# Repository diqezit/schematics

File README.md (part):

<details>
<summary><b>Русская версия README</b></summary>

# FMradio

ЧМ-приёмник на дискретных транзисторах с низкой промежуточной частотой, зарядовым частотным детектором, варикапной настройкой, автоматической подстройкой частоты и УНЧ на LM386.

- Диапазон: 88-108 МГц
- Питание: +9 В
- Нагрузка: 8 Ом
- Целевой размер платы: 50 x 70 мм
- Ток покоя тракта до УНЧ: около 23 мА

> Статус: инженерный разбор схемы и наброска печатной платы. Источник истины по номиналам и режимам - LTspice, файл `Fm.asc` (ревизия 05). Файл Multisim `Fm.ms14` сохранён как историческая ссылка предварительной серии ревизии 01 и для сверки топологии KiCad. Это не подтверждение работоспособности готового устройства и не комплект для изготовления.

Изменения ревизии 05:

1. Варикапы D1 входного контура и D5 гетеродина заменены с BB112 на BB844. Принята модель Cjo = 120 пФ, Vj = 0,75 В, M = 1,35. Расчётная кривая C(V) сверена с опорной таблицей, отклонение меньше 1 %.
2. Транзистор гетеродина 2N5401 заменён на BFT92. Для 2N5401 с fT = 300 МГц запуска на 101,9 МГц не получено из-за недостаточного запаса по граничной частоте. Для BFT92 паспортное fT равно 5 ГГц, упрощённая SPICE-модель даёт около 1 ГГц.
3. Пересчитаны контуры: L1 = 175 нГн, C3 = 4,1 пФ, C4 = 13,7 пФ; L2 = 138 нГн, C17 = 10 пФ, C18 = 36 пФ, C19 = 13,7 пФ.
4. Добавлена директива `.ic` для короткого окна звукового тракта без ожидания установления медленной петли АПЧ.
5. Нагрузка R22/C22 в АПЧ увеличена до R22 = 15 кОм и C22 = 47 мкФ. Расчётная постоянная времени составляет около 0,7 с.

Правило трёх документов. Номиналы и режимы нормативны по LTspice. Топология и посадочные места нормативны по KiCad. Расчётные формулы разделов 1-7 записаны в нумерации KiCad/README и сверяются с LTspice по таблице соответствия. Перенумерация KiCad под ревизию 05 запланирована; до её выполнения таблица соответствия нормативна.

Расчётные величины в основных разделах получены аналитически для режимов по постоянному току и RC-цепей при U_БЭ около 0,65 В и типичном h21э транзисторов. Результаты симуляции сведены в приложении, совпадения и расхождения с расчётом отмечены явно. Ни расчёт, ни симуляция не заменяют измерений на реальной плате.

## Схема

## Демонстрация работы

Снимок относится к одному из прогонов подгонки контуров ревизии 01 в Multisim и служит только иллюстрацией настройки. Рабочие данные ревизии 05 сняты в LTspice командой `.tran 0 12m 10m 1n`. Raw-файл или экспорт ключевых трасс следует хранить вместе с `Fm.asc`.

## Источники и воспроизводимость

- `Fm_radio.kicad_sch`: схема, KiCad 10.0, лист A3.
- `Fm_radio.kicad_pcb`: печатная плата, KiCad 10.0, два слоя меди F.Cu и B.Cu.
- `Fm_radio.kicad_pro`: настройки проекта, включая правила проверки платы.
- `Fm_radio.kicad_prl`: локальные настройки отображения.
- `Fm.asc`: файл симуляции LTspice, источник истины начиная с ревизии 02. Содержит нетлист, директивы `.tran`, `.op`, `.ic`, `.options`, модели диодов, варикапов и транзистора гетеродина.
- `Fm.ms14`: файл симуляции Multisim. Содержит экспорт предварительной серии ревизии 01 и замеры рабочей точки. Результаты ревизий 02-05 из него не воспроизводятся и не цитируются как текущие.

## Инструмент моделирования и соответствие ревизий

Начиная с ревизии 02 источником истины по номиналам и режимам является LTspice. Multisim оставлен как историческая ссылка ревизии 01 и средство сверки топологии KiCad.

LTspice выбран из-за доступных допусков интегрирования, именованных измерений, `.step`, `.meas`, `.op` и приемлемого времени расчёта. В Multisim непрерывные окна 300 мкс и 3 мс были практически недоступны, а встроенный частотомер давал ложные показания на узлах с амплитудой в десятки милливольт.

Модели LTspice, источник истины ревизии 05:

```text
.model BB844 D(Is=1e-14 Rs=0.28 N=1.0 Cjo=120p M=1.35 Vj=0.75 Fc=0.5
+ Bv=18 Ibv=10u Tt=0 Eg=1.11 Xti=3)

.model BFT92 PNP(IS=1E-14 BF=100 VAF=100 IKF=0.1 ISE=1E-13 NE=1.5
+ BR=4 IKR=0.1 ISC=1E-13 NC=1.5 RB=10 RE=1 RC=10
+ CJE=1.5P VJE=0.7 MJE=0.4 CJC=1P VJC=0.5 MJC=0.4
+ TF=0.15N TR=10N XTB=1.5 XTI=3 EG=1.11)

.model BZX55C6V8 D(Is=1e-14 N=1.1 Rs=3.5 Cjo=160p M=0.33 Vj=0.75 Bv=6.8 Ibv=5m Eg=1.11 Xti=3)
.model BZX55C3V3 D(Is=1e-14 N=1.1 Rs=15 Cjo=25p M=0.33 Vj=0.6 Bv=3.3 Ibv=5m)
```

Модель BB112 сохранена только для воспроизведения ревизии 04:

```text
.model BB112 D(Is=1e-14 Rs=0.7 N=1.2 Cjo=58p M=0.50 Vj=0.85 Fc=0.5 Bv=30 Ibv=10u Tt=0)
```

Упрощённая модель BFT92 с TF = 0,15 нс соответствует оценочному fT около 1 ГГц, а не паспортным 5 ГГц. Она подтверждает запуск в ревизии 05, но не заменяет модель производителя для оценки амплитуды, фазового шума и предельного режима. Имена библиотек остальных транзисторов и полные строки их SPICE-моделей в репозитории не зафиксированы, поэтому перед повторным прогоном модели следует сверить.

## Протокол прогонов

Нормативный короткий прогон ревизии 05:

```text
.tran 0 12m 10m 1n
.ic V(DETEC)=1.2 V(AFC)=1.2 V(FILT)=1.2 V(N010)=4.5 V(VZ_3V3)=3.3 V(VZ_6V8)=6.8
.options reltol=0.003 trtol=7 method=gear cshunt=1e-14 plotwinsize=0
```

Директива `.ic` задаёт начальные уровни детектора, АПЧ, фильтра, выхода LM386 и двух опорных шин. Она нужна для наблюдения последних 2 мс из окна 12 мс без ожидания установления петли АПЧ с постоянной времени около 0,7 с. Этот режим не доказывает захват АПЧ и не заменяет прогон без начальных условий.

Дополнительные прогоны:

- Рабочая точка: `.op` при V1 = 8/9/10 В, положении потенциометра 0/50/100 % и T = -10/25/50 C.
- ВЧ и ПЧ без принудительных начальных условий: не менее 300 мкс с максимальным шагом 1 нс.
- Звуковой тракт: не менее 20 мс либо до установления C25 = 330 мкФ и узла N010.
- АПЧ: 0,5-1 с без `.ic` или отдельная огибающая модель. Полный ВЧ-прогон с шагом 1 нс на таком интервале вычислительно тяжёл.
- Ограничитель: 3 мс с контролем VBE(VT5) не ниже -5 В и огибающей 1 кГц 280-400 мВ размаха.

## Нормативные пороги приёмки

Пороги ревизии 04 сохранены для исторического сравнения:

- меандр на коллекторе VT4 непрерывен до 300 мкс, без пачек и провалов;
- ток обратной связи УПЧ без дрейфа среднего;
- полка детектора 1,1-1,3 В;
- I(D6) 5-12 мА;
- V(REF) 6,4-7,2 В.

Нормативные пороги ревизии 05:

- размах на коллекторе Q6 1-2 В;
- ток эмиттера Q6 2-3 мА без двуполярных игл и выбросов;
- период импульсов ПЧ при MDI = 0 равен 2,35 +/- 0,05 мкс;
- полка детектора 1,1-1,3 В;
- I(D6) 5-12 мА;
- V(REF) 6,4-7,2 В;
- звуковой сигнал на нагрузке 8 Ом не меньше 1 В размаха после установления тракта.

Текущий прогон ревизии 05 проходит критерии периода ПЧ и полки детектора. Критерии амплитуды и тока гетеродина не пройдены. Ток D6 и установившиеся уровни опорных шин без `.ic` в предоставленных измерениях отсутствуют. Критерий звука не оценён, потому что V(N010) и C25 не установились в окне 12 мс.

## Блокеры до трассировки

- Перевозбуждение гетеродина. V(Q6_C) имеет размах 0-4 В, Ie(Q6) достигает примерно +/-6 мА. Требуется повторный расчёт смещения и коэффициента обратной связи BFT92. Плату до выбора проверенного режима не фиксировать.
- Сопряжение контуров. При одном управляющем напряжении разность резонансных частот L1 и L2 меняется примерно от 0,5 до 1,5 МГц вместо требуемых 425 кГц. Нужна раздельная коррекция ветвей D1 и D5 или подстроечные элементы.
- Ход настройки. Связка BB844 и 13,7 пФ в текущей модели даёт около 0,8 МГц, поэтому диапазон 88-108 МГц не перекрывается. Нужна коммутация L2, другой диапазон ёмкостей или отдельная грубая настройка.
- Сохраняется блокер ревизии 04: прогон 3 мс с VBE(VT5) не ниже -5 В ещё не выполнен.

Имена узлов вида n0XX не нормативны. Перед прогоном следует назначить метки A, B, REF, TUNE, Q1_E, Q2_B, Q3_B, Q4_C, Q5_C, Q6_C, DETEC, AFC, FILT, N010, SPK, VZ_3V3 и VZ_6V8.

## Таблица соответствия идентификаторов

Таблица нормативна до перенумерации KiCad.

| Назначение | KiCad/README | LTspice rev 05 | Номинал или тип |
|---|---|---|---|
| ВЧ-транзистор | VT1 2N5401 | Q1 2N5401 | режим без изменения |
| Смеситель | VT2 BF517 | Q2 2SC3838K | тип 2SC3838K |
| УПЧ 1 / УПЧ 2 | VT3 / VT4 BC547 | Q3 / Q4 BC547C | группа C |
| Ограничитель | VT5 BC547 | Q5 BC547C | группа C |
| Гетеродин | VT6 BFT92 | Q6 BFT92 | PNP, SOT-23 |
| Диоды детектора | VD1, VD2 1N4148 | D2, D3 1N4148 | без изменения |
| Опора настройки | VD3, R19 | D6 BZX55C6V8, R25 180 Ом | V(REF) около 6,86 В |
| Шина 3,3 В | VD4, R27 1 кОм | D4, R19 1 кОм | VZ_3V3 |
| Варикап входа | BB844, C4 13,7 пФ | D1 BB844, C4 13,7 пФ | Cjo = 120 пФ |
| Варикап гетеродина | BB844, C19 13,7 пФ | D5 BB844, C19 13,7 пФ | Cjo = 120 пФ |
| Входной контур | L1, C3, C4, D1 | L1 175 нГн, C3 4,1 пФ, C4 13,7 пФ | пересчитан в rev 05 |
| Контур гетеродина | L2, C17, C18, C19, D5 | L2 138 нГн, C17 10 пФ, C18 36 пФ, C19 13,7 пФ | пересчитан в rev 05 |
| Вход рейки | R2 22 Ом | R15 22 Ом | без изменения |
| Рейка A к рейке B | свободное обозначение | 100 Ом | номер сверить |
| Эмиттер ВЧ | R3 470 Ом | R1 470 Ом | без изменения |
| Делитель базы ВЧ | R4 6,8 кОм / R13 33 кОм | R2 6,8 кОм / R3 33 кОм | без изменения |
| База смесителя | R6 620 кОм | R4 620 кОм | без изменения |
| Нагрузка смесителя | R5 3 кОм, C3 47 пФ | R5 3 кОм, C6 47 пФ | 47 пФ обязателен |
| ФНЧ после смесителя | свободные обозначения | 470 Ом, 33 пФ NP0 | номера сверить с рейками |
| Серия после связи | R11 | R6 100 кОм | аттенюатор |
| ООС эмиттер-база | R12 | R7 2,2 кОм | слив заряда |
| Нагрузка УПЧ1 / УПЧ2 | R7 10 кОм / R8 2,2 кОм | R8 10 кОм / R9 2,2 кОм | без изменения |
| Эмиттер УПЧ2 | R14 470 Ом, C16 47 нФ | R10 470 Ом, C10 47 нФ | без изменения |
| База / нагрузка ограничителя | R9 47 кОм / R10 3 кОм | R12 47 кОм / R13 3 кОм | без изменения |
| Фильтр детектора | R15 10 кОм, C17 10 нФ | R12 10 кОм, C14 10 нФ | обозначения rev 05 |
| Связь смеситель-УПЧ | C8 | C7 1 нФ | без изменения |
| Связь УПЧ-ограничитель | C9 | C12 10 нФ | без изменения |
| Насос детектора | C10 | C13 39 пФ | без изменения |
| Потенциометр настройки | R21 10 кОм | U1 10 кОм | движок выставляется по периоду |
| АПЧ | R26/R25, C26 | R22 15 кОм, C22 47 мкФ | постоянная времени около 0,7 с |
| Выходной конденсатор УНЧ | C12 | C25 330 мкФ | время установления больше окна 12 мс |
| Байпас LM386 | по схеме | C27 | начальный заряд не установился |

Разделы 1-5 описывают тракт LTspice ревизии 05. Раздел 6 относится к модели и изделию с LM386. Раздел 7 совмещает топологию шин LTspice и требования к физической плате.

## Архитектура

```text
AE1 -> C6 -> Q1 / L1 / D1 -> Q2 -> Q3 -> Q4 -> Q5
                                                    |
                  LM386 <- volume <- detector <- D2 / D3 / C13
                    |                         |
                 C25 / 8R              R22 / C22 AFC
                                              |
                                 D1 / D5 / Q6 / L2
```

Сигнал антенны усиливается каскадом с общей базой и смешивается с сигналом гетеродина через магнитную связь L1-L2. Затем он проходит широкополосный бесконтурный усилитель промежуточной частоты, ограничивается и демодулируется зарядовым частотным детектором. Медленная составляющая напряжения детектора управляет варикапами через автоматическую подстройку частоты. Входной контур сопряжён с настройкой вторым варикапом BB844. Низкочастотный усилитель построен на LM386.

Элементная база ревизии 05: Q1 типа 2N5401, Q2 типа 2SC3838K, Q3-Q5 типа BC547C, Q6 типа BFT92, D1 и D5 типа BB844.

Промежуточная частота остаётся низкой:

```math
f_{IF} \approx 425 \text{ кГц}, \qquad f_{LO} = f_{RF} + 425 \text{ кГц}
```

При f_RF = 101,5 МГц целевая частота гетеродина равна примерно 101,925 МГц. Период 2,35 мкс соответствует 425 кГц. Источник SFFM с MDI = 75 и FS = 1 кГц даёт девиацию +/-75 кГц.

Низкая ПЧ не обеспечивает зеркальную избирательность. При верхней настройке зеркальный канал отстоит на 2f_IF, то есть примерно на 850 кГц, и остаётся внутри полосы входного контура. Для радикального улучшения нужен двухконтурный преселектор или двойное преобразование частоты.

## Шины питания

```text
+9 В -> развязка -> узел A -> развязка -> узел B
```

Узел A питает ограничитель. Узел B питает ВЧ-каскад, смеситель и усилитель промежуточной частоты. LM386 питается от +9 В с отдельной местной развязкой. Гетеродин BFT92 питается от шины VZ_3V3. Опора настройки D6 питается от +9 В через 180 Ом.

| Шина | Назначение | Нормальный уровень |
|---|---|---|
| +9 В | LM386, опорные стабилизаторы | 9,0 В |
| Узел A | ограничитель | после входной развязки |
| Узел B | Q1-Q4 | около 8,25-8,3 В |
| VZ_3V3 | Q6 BFT92 | 3,3 В |
| VZ_6V8 / REF | настройка и АПЧ | около 6,86 В |

Ток покоя около 23 мА относится к тракту до LM386. Ток и мощность полного изделия зависят от громкости и нагрузки 8 Ом.

## 1. Входной ВЧ-усилитель

Q1 2N5401 включён по схеме с общей базой. Сигнал антенны поступает на эмиттер через 1 нФ. Делитель 6,8 кОм / 33 кОм задаёт смещение базы, 10 нФ шунтирует базу по ВЧ, 470 Ом задаёт ток эмиттера. Коллектор нагружен контуром L1 = 175 нГн.

В ревизии 05 контур содержит C3 = 4,1 пФ и ветвь C4 = 13,7 пФ с D1 BB844. Обратное смещение D1 приходит с цепи настройки через резистор. Номиналы относятся к LTspice и не заменяют измерение реальной индуктивности, паразитной ёмкости и добротности.

Ёмкость модели BB844 оценивается выражением:

```math
C(V) = \frac{C_{jo}}{(1 + V/V_j)^M}, \qquad C_{jo}=120 \text{ пФ}, \quad V_j=0{,}75 \text{ В}, \quad M=1{,}35
```

Расчётная кривая сверена с опорной таблицей с отклонением меньше 1 %. Это подтверждает параметры модели, но не гарантирует сопряжение двух реальных контуров с разбросом L и паразитных ёмкостей.

Режим по постоянному току не менялся принципиально. В ревизии 05 Ie(Q1) около -1,47 мА. На эмиттере Q1 присутствует ВЧ-сигнал 101,5 МГц с размахом примерно 0-400 мВ, то есть сигнал доходит до входа смесителя.

Катушка L1 в исходной механике наматывается проводом 0,5 мм на оправке 5,5 мм. Число витков и шаг следует подобрать по измеренным 175 нГн, а не переносить автоматически из расчёта ревизии 04.

## 2. Смеситель

Q2 2SC3838K включён по схеме с общим эмиттером. Резистор 620 кОм задаёт ток базы, 3 кОм служит коллекторной нагрузкой, 47 пФ подавляет остатки ВЧ и ограничивает верхнюю частоту низкой ПЧ. Связь с усилителем промежуточной частоты идёт через разделительную цепь и аттенюатор 100 кОм.

Связь входного контура с базой смесителя должна иметь ёмкость порядка единиц пикофарад. Номинал 1 нФ из ранней схемы перегружает контур. Электролит 2,2 мкФ в ВЧ-узле исключается.

Полюс нагрузки смесителя:

```math
f_p = \frac{1}{2\pi \times 3\text{ кОм} \times 47\text{ пФ}} \approx 1{,}13 \text{ МГц}
```

Конденсатор 47 пФ обязателен. Без него остаток гетеродина выпрямляется следующим каскадом, Q3 насыщается, а тракт ПЧ защёлкивается.

В ревизии 05 V(Q2_B) меняется примерно от 350 до 900 мВ. Ic(Q2) меняется примерно от 0,3 до 3,6 мА. Смеситель работает в ключевом режиме, но инжекция гетеродина выше желаемой. Уменьшать её следует после нормализации режима Q6, а не случайным ослаблением ПЧ-тракта.

Магнитная связь L1-L2 остаётся двусторонней. Для платы требуются контролируемые ориентация и расстояние между катушками. Точное соответствие коэффициента K геометрии платы модель SPICE не рассчитывает.

### RC после смесителя

Дополнительный ФНЧ 470 Ом / 33 пФ должен стоять сразу после коллекторной нагрузки смесителя. Его расчётный полюс:

```math
f_p = \frac{1}{2\pi \times 470 \times 33\text{ пФ}} \approx 10{,}26 \text{ МГц}
```

На 425 кГц звено практически прозрачно, а остатки диапазона 88-108 МГц ослабляются. Обозначения этого фильтра конфликтовали с обозначениями развязки питания в ранних версиях и должны быть назначены заново в KiCad.

## 3. Усилитель промежуточной частоты

Q3 и Q4 BC547C образуют двухкаскадный усилитель с непосредственной связью. После связи со смесителем стоит 100 кОм, а с эмиттера Q4 на базу Q3 включён резистор 2,2 кОм. Эта пара ограничивает привод и отводит выпрямленный заряд за период ПЧ.

Эмиттер Q4 нагружен 470 Ом с шунтом 47 нФ. Связь с ограничителем идёт через 10 нФ. Номиналы усилителя промежуточной частоты в ревизии 05 не менялись.

Для периода 2,35 мкс постоянная времени слива около 2,2 мкс остаётся сопоставимой с одним циклом:

```math
\tau_{drain} \approx 2{,}2 \text{ кОм} \times 1 \text{ нФ} \approx 2{,}2 \text{ мкс}
```

Критерий работы каскада: непрерывные импульсы ПЧ без перехода в линейный режим и без дрейфа среднего тока обратной связи. Прямого отдельного набора измерений Q3/Q4 для ревизии 05 не предоставлено, поэтому прежние амплитуды ревизии 04 не объявляются текущими.

## 4. Ограничитель и детектор

Q5 BC547C работает ограничителем. Резистор 47 кОм задаёт ток базы, 3 кОм служит нагрузкой, эмиттер соединён с общим проводом. В ревизии 05 V(Q5_C) имеет прямоугольную форму 0-11 В с периодом 2,35 мкс, что соответствует ПЧ около 425 кГц.

Обратное напряжение база-эмиттер ограничителя остаётся открытым риском. Стандартная BJT-модель может не отражать реальный пробой. До прогона 3 мс с VBE(VT5) не ниже -5 В этот пункт не закрыт.

Зарядовый детектор построен на C13 = 39 пФ и двух 1N4148. Средний ток насоса оценивается так:

```math
I_{avg} = C \times \Delta U \times f_{IF}, \qquad U_{det} = I_{avg} \times R_{load}
```

При ПЧ около 425 кГц ожидаемая полка находится около 1,2 В. В ревизии 05 V(DETEC) равно 1,2 В, то есть детектор находится в штатной точке.

Фильтр ревизии 05 обозначен R12 = 10 кОм и C14 = 10 нФ. Без нагрузки:

```math
\tau_0 = 10 \text{ кОм} \times 10 \text{ нФ} = 100 \text{ мкс}
```

С нагрузкой цепи АПЧ эффективная постоянная времени оценивается примерно в 60 мкс. Вариант C14 = 4,7 нФ даёт 47 мкс без нагрузки, но не принят до проверки звуковой АЧХ и уровня пульсаций.

## 5. Гетеродин и автоматическая подстройка частоты

Q6 BFT92 с L2 = 138 нГн образует генератор Колпитца. Ёмкостная обратная связь задаётся C17 = 10 пФ и C18 = 36 пФ. Варикап D5 BB844 включён через C19 = 13,7 пФ. База заземлена по переменному току, питание приходит от стабилизированной шины 3,3 В.

Эквивалентная последовательная ёмкость делителя обратной связи:

```math
C_s = \frac{10 \times 36}{10 + 36} \approx 7{,}83 \text{ пФ}
```

2N5401 с модельным fT = 300 МГц не запускался на 101,9 МГц. BFT92 имеет паспортное fT = 5 ГГц, а применённая упрощённая модель соответствует примерно 1 ГГц. Замена восстановила запуск, но одновременно дала избыточную амплитуду.

Текущий результат:

- V(Q6_C) колеблется от 0 до 4 В;
- Ie(Q6) имеет выбросы примерно до +/-6 мА;
- период импульсов ПЧ равен 2,35 мкс;
- V(Q2_B) показывает избыточную инжекцию в смеситель.

Требуемый режим Q6 составляет 1-2 В размаха на коллекторе и 2-3 мА эмиттерного тока без выбросов. Номиналы коррекции обратной связи и смещения пока не утверждены. В исходных данных одновременно предложены несовместимые направления изменения C17 и R16, поэтому ни один вариант не считается нормативным до параметрического прогона и проверки на макете.

Цепь АПЧ содержит R22 = 15 кОм и C22 = 47 мкФ:

```math
\tau_{AFC} = 15 \text{ кОм} \times 47 \text{ мкФ} = 0{,}705 \text{ с}
```

В 12 мс V(AFC) равно 1,2009 В и практически не меняется. Это ожидаемо, потому что окно составляет меньше 2 % постоянной времени. Начальное условие V(AFC) = 1,2 В позволяет наблюдать ВЧ, ПЧ и начало звука, но не подтверждает захват и удержание АПЧ.

Знак петли при верхней настройке:

```text
f_IF растёт -> U_det растёт -> управляющее напряжение меняет C_var -> f_LO снижается -> f_IF уменьшается
```

Полярность следует подтвердить отдельным малосигнальным прогоном, потому что расположение анода и катода BB844 и знак сумматора определяют фактическое направление коррекции.

## 6. Низкочастотный усилитель

Низкочастотный усилитель выполнен на LM386 с нагрузкой 8 Ом. В отличие от ревизии 04, узлы N010 и SPK присутствуют в прогоне ревизии 05.

Выходной разделительный конденсатор C25 = 330 мкФ вместе с нагрузкой имеет оценочную постоянную времени:

```math
\tau_{out} = 8 \text{ Ом} \times 330 \text{ мкФ} \approx 2{,}64 \text{ мс}
```

Однако установление всего тракта определяется также смещением LM386, байпасом C27, фильтром и начальными условиями. В конце окна V(N010) равно 5,78 В вместо ожидаемых примерно 4,5 В, а V(SPK) имеет только около 13 мВ размаха. Эти числа относятся к переходному процессу и не являются установившейся выходной мощностью.

Критерий ревизии 05 требует не менее 1 В размаха на 8 Ом после установления. Для его проверки нужен более длинный прогон, контроль среднего V(N010), напряжения на C27 и отсутствие ограничения LM386.

На плате у LM386 обязательны 100 нФ непосредственно между выводами питания и не менее 10 мкФ местной низкочастотной развязки. Цепь Бушеро должна иметь однозначные обозначения и единицы номиналов.

## 7. Питание

Питание ВЧ-каскада, смесителя, усилителя промежуточной частоты и ограничителя следует разводить отдельными RC-звеньями. Типовое звено: 100 Ом и 100 нФ, при необходимости 10 мкФ параллельно 100 нФ. Земля каждого конденсатора возвращается к местной опорной точке каскада.

Электролитические конденсаторы из-за паразитной индуктивности не обеспечивают развязку около 100 МГц. Параллельно каждому электролиту ставится керамика 100 нФ с минимальной длиной соединений.

Источник питания в модели идеальный. Реальное проникновение импульсов LM386 в шины ВЧ и ПЧ проверяется на макете или в отдельной модели с внутренним сопротивлением источника и паразитными параметрами платы.

## Известные ограничения макета

- Зеркальный канал на расстоянии около 850 кГц архитектурой практически не подавляется.
- Текущий ход настройки около 0,8 МГц не перекрывает 88-108 МГц.
- Сопряжение L1 и L2 от одного управляющего напряжения не достигнуто: разность частот меняется примерно от 0,5 до 1,5 МГц.
- Гетеродин BFT92 перевозбуждён: V(Q6_C) 0-4 В, Ie(Q6) до примерно +/-6 мА.
- Короткая модель BFT92 соответствует примерно 1 ГГц, а не паспортным 5 ГГц, поэтому амплитуда и ток требуют проверки с моделью производителя.
- АПЧ с R22 = 15 кОм и C22 = 47 мкФ не проверена на захват и удержание без `.ic`.
- V(AFC) = 1,2009 В в окне 12 мс показывает только отсутствие заметного движения на коротком интервале.
- Звуковой выход 13 мВ снят до установления C25, C27 и рабочей точки LM386.
- V(N010) = 5,78 В вместо 4,5 В относится к переходному процессу и требует длинного прогона.
- Обратное VBE ограничителя не проверено в обязательном окне 3 мс.
- Деэмфазис с C14 = 10 нФ составляет около 60 мкс под расчётной нагрузкой, вариант 4,7 нФ не проверен.
- LM386 и питание смоделированы без всех паразитных параметров реальной платы.
- При Vz = 7,2 В и V1 = 8 В колено опорного стабилитрона может не гарантироваться.
- Нумерация KiCad, BOM и LTspice расходится; таблица соответствия нормативна до перенумерации.
- BB844 является сдвоенным варикапом в SOT-23. Использование секций и распиновка на плате должны быть сверены с конкретным исполнением.

## Приложение. Паспорт блока по симуляции

### A.0. Структура файла симуляции Multisim

Экспорт `Fm.ms14` относится к предварительной серии ревизии 01. Временные метки немонотонны, каждая строка хранит два снимка нескольких безымянных узлов, а полный временной ряд отсутствует. Длительность отдельных прогонов около 30 мкс достаточна для ВЧ и ПЧ, но недостаточна для звука и АПЧ.

| Кривая | Характерный диапазон | Историческая интерпретация |
|---|---|---|
| 1 | -7...+4 В | контур гетеродина |
| 2 | 0 В +/-1-2 мВ | анод варикапа |
| 3 | -0,7...+0,8 В | узел насоса детектора |
| 4 | 3,3-3,6 В | коллектор смесителя или УПЧ |
| 5 | 0...0,7 В | вероятный выход детектора |
| 6 | 9,000 В | идеальная шина питания |

По этому экспорту нельзя оценивать постоянные времени, установление гетеродина, дрейф частоты, звук или АПЧ. Данные ревизии 05 в `Fm.ms14` не переносятся.

### A.1. Режимы по постоянному току

| Узел / каскад | Расчёт или норма | Симуляция | Ревизия | Вывод |
|---|---|---|---|---|
| VZ_3V3 | 3,3 В | 3,3 В по `.ic`, установившееся значение отдельно не дано | 05 | опору проверить без `.ic` |
| VZ_6V8 / REF | около 6,8 В | 6,8 В по `.ic`, ранее 6,86 В | 05 / 04 | критерий 6,4-7,2 В |
| Q1 | около 1,5 мА | Ie(Q1) около -1,47 мА | 05 | режим нормальный |
| Q2 | ключевой режим | Ic(Q2) 0,3-3,6 мА | 05 | инжекция повышена |
| Q3 / Q4 | режим rev 04 без изменения номиналов | отдельных DC-данных rev 05 нет | 05 | требует `.op`-таблицы |
| Q5 | ограничение | V(Q5_C) 0-11 В | 05 | импульсы ПЧ есть |
| Q6 BFT92 | 2-3 мА по критерию | Ie(Q6) до примерно +/-6 мА | 05 | перевозбуждение |
| DETEC | 1,1-1,3 В | 1,2 В | 05 | норма |
| AFC | медленная петля | 1,2009 В за 12 мс | 05 | захват не проверен |
| N010 | около половины 9 В | 5,78 В | 05 | переходный процесс |
| SPK | не меньше 1 В размаха | около 13 мВ размаха | 05 | звук не установился |

### A.2. Замеры по переходным процессам

#### Ревизия 05, LTspice, окно 10-12 мс

| Параметр | Значение | Статус | Комментарий |
|---|---|---|---|
| Команда | `.tran 0 12m 10m 1n` | действителен | сохранены последние 2 мс |
| Вход Q1 | 0-400 мВ, 101,5 МГц | действителен | сигнал доходит до смесителя |
| Ie(Q1) | около -1,47 мА | действителен | рабочий режим |
| V(Q2_B) | 350-900 мВ | превышение | инжекция гетеродина велика |
| Ic(Q2) | 0,3-3,6 мА | действителен | ключевой режим смесителя |
| V(Q5_C) | 0-11 В | действителен | импульсы ПЧ |
| Период V(Q5_C) | 2,35 мкс | проходит | ПЧ около 425 кГц |
| V(Q6_C) | 0-4 В | не проходит | критерий 1-2 В размаха |
| Ie(Q6) | примерно +/-6 мА | не проходит | критерий 2-3 мА без выбросов |
| V(DETEC) | 1,2 В | проходит | нормальная полка |
| V(AFC) | 1,2009 В | не оценён | за 12 мс петля не устанавливается |
| V(N010) | 5,78 В | переходный | ожидаемый покой около 4,5 В |
| V(SPK) | около 13 мВ размаха | не оценён | звуковой тракт не установился |

#### Ревизия 04, LTspice, историческая рабочая точка

| Параметр | Значение | Статус |
|---|---|---|
| Центральная ПЧ | около 425 кГц | исторический |
| Период при MDI = 0 | 2,35 мкс | исторический |
| Полка детектора | 1,17-1,195 В | исторический |
| Звуковой сигнал детектора | около 360 мВ размаха | исторический |
| Инжекция на базе смесителя | 0,36-0,8 В размаха | исторический |
| Варикапы | BB112, Cjo = 58 пФ | заменены |
| Гетеродин | 2N5401 | заменён |

#### Ревизия 01, Multisim, предварительная серия

| Параметр | Значение | Статус |
|---|---|---|
| ПЧ отдельных прогонов | 250-400 кГц | исторический |
| Полка детектора | 0,40-0,50 В | исторический |
| k = 0,15 | уход 10-15 МГц | подтверждает ограничение связи |
| Запуск гетеродина | устойчивый в отдельных конфигурациях | не относится к rev 05 |

### A.3. Методика и ограничения модели

- Источник истины ревизии 05 - LTspice `Fm.asc`. Multisim используется только для истории ревизии 01.
- Частоту определяют курсорами по периоду при MDI = 0 внутри одного непрерывного участка.
- `.ic` ускоряет выход в выбранную окрестность рабочей точки, но скрывает естественный запуск медленных цепей. Все выводы об АПЧ и LM386 подтверждаются повторным прогоном без `.ic`.
- Модель BFT92 упрощена и имеет оценочное fT около 1 ГГц. Для амплитуды, тока и устойчивости требуется модель производителя и макет.
- Связь L1-L2 в SPICE задана коэффициентом K. Геометрия, экран, земля под катушками и паразитные связи платы не моделируются.
- Критерий звука применяется только после установления N010, C25 и C27.
- Для SFFM используется синтаксис `SFFM(VO VA FC MDI FS)`. При VO = 0, VA = 1m, FC = 101.5Meg, MDI = 75, FS = 1k девиация равна 75 кГц.
- B-source может задавать тот же сигнал выражением `V=0.001*sin(2*pi*101500000*time+75*sin(2*pi*1000*time))`. Утверждение о конкретном ускорении не считается нормативным без сравнения на одной машине и с одинаковыми допусками.

### A.4. Открытые вопросы

1. Калибровка гетеродина. Закрыто для точки ревизии 04. Для ревизии 05 период 2,35 мкс получен, но режим Q6 не проходит по амплитуде и току.
2. Модуляция 1 кГц в коротком окне. Частично закрыто в ревизии 04. Для ревизии 05 установившийся звук не получен.
3. Захват и удержание АПЧ, развязка УНЧ и рейки, мощность LM386 и КНИ. Открыто. Нужен длинный прогон без `.ic` или макет.
4. Измерение L1, L2 и рабочей ёмкости варикапов на конкретной плате. Открыто. Модельные 175 нГн и 138 нГн переносятся в BOM только после выбора конструкции катушек.
5. Непрерывный прогон с фиксированными параметрами. Закрыто для короткого окна ревизии 05, не закрыто для АПЧ и звука.
6. Обратное VBE ограничителя. Открыто. Нужен прогон 3 мс с VBE(VT5) не ниже -5 В.
7. Опора D6. Закрыто в ревизии 04, для ревизии 05 требуется повторный `.op` без принудительного V(VZ_6V8).
8. Устойчивость усилителя промежуточной частоты. Закрыто в ревизии 04. Для ревизии 05 номиналы не менялись, но отдельная таблица токов Q3/Q4 не снята.
9. Пульсация анода варикапа. Старое измерение BB112 не переносится на BB844. Открыто.
10. Конденсатор деэмфазиса. Текущие 10 нФ дают 100 мкс без нагрузки и около 60 мкс с расчётной нагрузкой. Выбор не закрыт.
11. Перевозбуждение гетеродина. V(Q6_C) имеет размах 0-4 В, Ie(Q6) достигает примерно +/-6 мА при критерии 1-2 В и 2-3 мА. В исходных заметках предложены C17 = 4,7 пФ или изменение R16 до 680 Ом, но обозначение R16 и направление изменения C17 описаны противоречиво. До параметрического прогона ни один номинал не принят.
12. Сопряжение контуров. При одном управляющем напряжении разность частот меняется примерно от 0,5 до 1,5 МГц вместо 0,425 МГц. Нужны раздельная коррекция D1/D5 или подстроечные элементы. Открыто.
13. Ход настройки. BB844 с C4 = C19 = 13,7 пФ даёт около 0,8 МГц по имеющимся данным и не перекрывает 88-108 МГц. Способ грубой укладки диапазона не выбран. Открыто.
14. Деэмфазис. Для R12 = 10 кОм и C14 = 10 нФ постоянная времени без нагрузки равна 100 мкс, с нагрузкой АПЧ около 60 мкс. C14 = 4,7 нФ даёт 47 мкс без нагрузки. Нужны АЧХ и измерение с фактической нагрузкой LM386. Открыто.

Замечание по обозначениям. В исходных данных критерий периода относится к коллектору VT4, а таблица ревизии 05 приводит V(Q5_C). До перенумерации следует считать нормативными частоту 425 кГц и период 2,35 мкс, а конкретную контрольную точку подтвердить по `Fm.asc` и таблице соответствия.

## Исправления к схеме и плате

1. ПЧ. Рабочая частота задаётся процедурой настройки f_LO = f_RF + 425 кГц. Период при MDI = 0 равен 2,35 +/- 0,05 мкс.
2. Катушки. Число витков, диаметр и шаг закрепляются по измеренным L1 и L2. Значения витков из ревизии 04 не гарантируют 175 нГн и 138 нГн.
3. ВЧ-связь. Электролит 2,2 мкФ исключить, связь с базой смесителя выполнить NP0/C0G номиналом порядка единиц пикофарад.
4. Конденсатор 47 пФ на коллекторе смесителя обязателен. Без него усилитель промежуточной частоты защёлкивается остатком гетеродина.
5. Эмиттер Q2. Вариант стабилизации 100-220 Ом с ВЧ-шунтом не принят без проверки.
6. Связь L1-L2. На плате нужны контролируемые ориентация и расстояние. Ёмкостную связь вместо магнитной не добавлять без отдельного расчёта.
7. Питание стабилитрона 3,3 В. Резистор 1 кОм подключается к +9 В.
8. Цепь Бушеро. Указать единицу ёмкости и присвоить уникальные обозначения.
9. Опора настройки. D6 BZX55C6V8 и R25 = 180 Ом сохраняются до повторного `.op` ревизии 05.
10. LM386. Добавить 100 нФ у выводов питания и местный электролит не менее 10 мкФ.
11. Развязка рейки от УНЧ. Проверить 100 Ом и 100 мкФ на макете с максимальной громкостью.
12. Деэмфазис. Не менять R12/C14 без измерения АЧХ и нагрузки АПЧ/LM386.
13. ВЧ-транзисторы. Q1 2N5401 остаётся предельным по fT; гетеродин переведён на BFT92.
14. Входной контур и зеркальный канал. Низкая ПЧ не даёт достаточного подавления зеркала, это ограничение архитектуры.
15. Обозначение фильтра детектора. Привести схему, BOM и плату к R12/C14 либо к другой единой паре без конфликтов.
16. ВЧ-развязка электролитов. Параллельно каждому электролиту поставить 100 нФ с коротким возвратом в землю.
17. Резистор между рейками и ФНЧ после смесителя. Назначить свободные обозначения, не пересекающиеся с АПЧ.
18. Перекрытие диапазона. Предусмотреть грубую укладку частоты, потому что электронный ход существенно меньше 20 МГц.
19. Усилитель промежуточной частоты. Сохранить 100 кОм последовательно и 2,2 кОм обратной связи, пока новый прогон не докажет другое.
20. Опора настройки D6. Питание через 180 Ом от +9 В, затем повторная установка U1 по периоду.
21. Блокирующий пункт ревизии 04. Не фиксировать плату до прогона 3 мс с контролем обратного VBE ограничителя.
22. Варикапы ревизии 05. D1 и D5 заменить на BB844 с моделью Cjo = 120 пФ, Vj = 0,75 В, M = 1,35. Для SOT-23 проверить общую катодную точку и назначение выводов. Не переносить посадочное место BB112 без проверки корпуса.
23. Гетеродин ревизии 05. Q6 заменить с 2N5401 на BFT92. Посадочное место SOT-23 и распиновку сверить с паспортом. Режим смещения и обратной связи не фиксировать до устранения тока примерно +/-6 мА.
24. Входной контур ревизии 05. Установить расчётные L1 = 175 нГн, C3 = 4,1 пФ, C4 = 13,7 пФ. Предусмотреть площадку для подстройки, потому что точное сопряжение не подтверждено.
25. Контур гетеродина ревизии 05. Установить расчётные L2 = 138 нГн, C17 = 10 пФ, C18 = 36 пФ, C19 = 13,7 пФ. Значения считать стартовыми для макета, а не гарантией перекрытия диапазона.
26. Начальные условия. Добавить директиву `.ic` только в профиль короткого прогона. Профиль проверки запуска, звука и АПЧ должен выполняться без принудительных начальных напряжений.
27. Фильтр АПЧ. Установить R22 = 15 кОм и C22 = 47 мкФ. Постоянная времени около 0,705 с. Полярность электролита и возврат земли проверить по реальному знаку напряжения.
28. Блокирующие пункты ревизии 05. До трассировки закрыть перевозбуждение Q6, сопряжение L1/L2 и способ перекрытия 88-108 МГц. Результат 13 мВ на SPK не считать отказом или приёмкой до установления LM386.

## Итоги

Ревизия 05 сохраняет архитектуру супергетеродинного ЧМ-приёмника 88-108 МГц с низкой ПЧ около 425 кГц, зарядовым детектором, варикапной настройкой, автоматической подстройкой частоты и LM386. D1 и D5 заменены на BB844, гетеродин переведён с 2N5401 на BFT92. Контуры пересчитаны на L1 = 175 нГн, C3 = 4,1 пФ, C4 = 13,7 пФ и L2 = 138 нГн, C17 = 10 пФ, C18 = 36 пФ, C19 = 13,7 пФ.

Короткий прогон подтверждает прохождение ВЧ-сигнала, ключевой режим смесителя, ПЧ около 425 кГц и полку детектора 1,2 В. Одновременно он показывает перевозбуждение BFT92: 0-4 В на коллекторе и ток до примерно +/-6 мА. АПЧ за 12 мс не успевает измениться из-за постоянной времени около 0,7 с. V(N010) = 5,78 В и V(SPK) около 13 мВ относятся к неустановившемуся звуковому тракту.

Печатная плата остаётся наброском. До её фиксации нужно нормализовать режим Q6, обеспечить сопряжение контуров, выбрать способ грубой укладки полного диапазона, проверить обратное VBE ограничителя и выполнить длинный прогон звука и АПЧ без `.ic`. Открытые вопросы перечислены в приложении A.4.

## Ссылки

- TI LM386: https://www.ti.com/product/LM386
- onsemi BC546 / BC547 / BC548: https://www.onsemi.com/pdf/datasheet/bc546-d.pdf
- onsemi 2N5401: https://www.onsemi.com/pdf/datasheet/2n5401-d.pdf
- ROHM 2SC3838K: https://www.rohm.com/products/transistors/bipolar-transistors/standard-bipolar-transistors/2sc3838k-product
- NXP BFT92: https://www.nxp.com/products/BFT92
- Infineon BB844: https://www.alldatasheet.com/datasheet-pdf/pdf/396152/INFINEON/BB844.html
- Siemens BB112, историческая модель ревизии 04: https://www.alldatasheet.com/datasheet-pdf/pdf/44230/SIEMENS/BB112.html
- Vishay BZX55: https://www.vishay.com/docs/85604/bzx55.pdf

</details>

<details>
<summary><b>English version README</b></summary>

# FMradio

FM receiver built with discrete transistors, a low intermediate frequency, a charge-pump frequency detector, varicap tuning, automatic frequency control, and an LM386 audio amplifier.

- Band: 88-108 MHz
- Supply: +9 V
- Load: 8 ohm
- Target board size: 50 x 70 mm
- Quiescent current through the detector chain: about 23 mA

> Status: engineering review of the schematic and PCB draft. The source of truth for values and operating points is LTspice, file `Fm.asc` revision 05. The Multisim file `Fm.ms14` is retained as a historical revision 01 reference and for KiCad topology checks. This is neither confirmation of a working receiver nor a fabrication-ready release.

Revision 05 changes:

1. Input-tank D1 and oscillator D5 were changed from BB112 to BB844. The model uses Cjo = 120 pF, Vj = 0.75 V, and M = 1.35. The calculated C(V) curve was checked against the reference table with less than 1 percent deviation.
2. The oscillator transistor was changed from a 2N5401 to a BFT92. The 2N5401 with fT = 300 MHz did not start at 101.9 MHz because of insufficient transition-frequency margin. The BFT92 datasheet value is 5 GHz; the simplified SPICE model gives about 1 GHz.
3. The tanks were recalculated: L1 = 175 nH, C3 = 4.1 pF, C4 = 13.7 pF; L2 = 138 nH, C17 = 10 pF, C18 = 36 pF, C19 = 13.7 pF.
4. An `.ic` directive was added for short audio-window inspection without waiting for the slow AFC loop to settle.
5. The AFC R22/C22 load was increased to R22 = 15 kOhm and C22 = 47 uF, for a calculated time constant of about 0.7 s.

Three-document rule. Values and operating points are normative from LTspice. Topology and footprints are normative from KiCad. Formulae in sections 1-7 use the KiCad/README designators and must be cross-checked against LTspice with the correspondence table. Until KiCad is renumbered for revision 05, that table is normative.

Neither calculation nor simulation replaces measurements on a real board.

## Schematic

## Demonstration

The image belongs to a revision 01 Multisim alignment run and is only an illustration. Revision 05 working data comes from the LTspice command `.tran 0 12m 10m 1n`. Store the raw file or exported key traces with `Fm.asc`.

## Sources and reproducibility

- `Fm_radio.kicad_sch`: KiCad 10.0 schematic, A3 sheet.
- `Fm_radio.kicad_pcb`: KiCad 10.0 two-layer PCB.
- `Fm_radio.kicad_pro`: project and DRC settings.
- `Fm_radio.kicad_prl`: local display settings.
- `Fm.asc`: LTspice simulation, source of truth from revision 02 onward. It contains the netlist, `.tran`, `.op`, `.ic`, and `.options` directives and the device models.
- `Fm.ms14`: historical Multisim revision 01 preliminary-series export. Revision 02-05 results are not reproduced from it and must not be quoted as current.

## Simulation tool and revision correspondence

From revision 02 the source of truth for values and operating points is LTspice. Multisim remains a revision 01 historical reference and a means of checking KiCad topology.

LTspice is used because it exposes integration tolerances, supports `.step`, `.meas`, `.op`, and named nodes, and completes the required windows in practical time. In Multisim, continuous 300 us and 3 ms windows were effectively unreachable, and the built-in counter produced false readings on nodes with tens-of-millivolt amplitude.

Revision 05 source-of-truth models:

```text
.model BB844 D(Is=1e-14 Rs=0.28 N=1.0 Cjo=120p M=1.35 Vj=0.75 Fc=0.5
+ Bv=18 Ibv=10u Tt=0 Eg=1.11 Xti=3)

.model BFT92 PNP(IS=1E-14 BF=100 VAF=100 IKF=0.1 ISE=1E-13 NE=1.5
+ BR=4 IKR=0.1 ISC=1E-13 NC=1.5 RB=10 RE=1 RC=10
+ CJE=1.5P VJE=0.7 MJE=0.4 CJC=1P VJC=0.5 MJC=0.4
+ TF=0.15N TR=10N XTB=1.5 XTI=3 EG=1.11)

.model BZX55C6V8 D(Is=1e-14 N=1.1 Rs=3.5 Cjo=160p M=0.33 Vj=0.75 Bv=6.8 Ibv=5m Eg=1.11 Xti=3)
.model BZX55C3V3 D(Is=1e-14 N=1.1 Rs=15 Cjo=25p M=0.33 Vj=0.6 Bv=3.3 Ibv=5m)
```

The BB112 model is retained only to reproduce revision 04:

```text
.model BB112 D(Is=1e-14 Rs=0.7 N=1.2 Cjo=58p M=0.50 Vj=0.85 Fc=0.5 Bv=30 Ibv=10u Tt=0)
```

The simplified BFT92 model with TF = 0.15 ns represents an approximate fT near 1 GHz rather than the 5 GHz datasheet value. It is adequate to demonstrate startup but not to certify amplitude, phase noise, or the limiting regime. Library names and the full SPICE model lines of the remaining transistors are not pinned in the repository, so the models must be re-checked before any repeat run.

Position numbers and some values in the LTspice revision do not match the KiCad schematic or the text of sections 1-7. Any number moved between documents must be cross-checked against the correspondence table. Before routing, bring the schematic, BOM, and PCB to one numbering.

## Run protocol

Normative short revision 05 run:

```text
.tran 0 12m 10m 1n
.ic V(DETEC)=1.2 V(AFC)=1.2 V(FILT)=1.2 V(N010)=4.5 V(VZ_3V3)=3.3 V(VZ_6V8)=6.8
.options reltol=0.003 trtol=7 method=gear cshunt=1e-14 plotwinsize=0
```

The `.ic` directive places the detector, AFC, filter, LM386 output, and reference rails near the intended operating point so the final 2 ms of a 12 ms run can be inspected. It does not prove natural startup, AFC capture, or full audio settling.

Additional runs:

- `.op` at V1 = 8/9/10 V, tuning control 0/50/100 percent, T = -10/25/50 C.
- RF and IF without forced initial conditions: at least 300 us with a maximum step of 1 ns.
- Audio: at least 20 ms or until C25, C27, and N010 settle.
- AFC: 0.5-1 s without `.ic`, or a separate envelope model.
- Limiter: 3 ms with VBE(VT5) no lower than -5 V and a 1 kHz envelope of 280-400 mV pp.

## Normative acceptance thresholds

Revision 04 thresholds are kept for historical comparison:

- the square wave at the VT4 collector is continuous to 300 us, with no bursts or dropouts;
- the IF feedback current shows no drift of its mean;
- detector plateau 1.1-1.3 V;
- I(D6) 5-12 mA;
- V(REF) 6.4-7.2 V.

Revision 05 thresholds:

- Q6 collector amplitude 1-2 V pp;
- Q6 emitter current 2-3 mA without bipolar spikes;
- IF pulse period at MDI = 0 equal to 2.35 +/- 0.05 us;
- detector plateau 1.1-1.3 V;
- I(D6) 5-12 mA;
- V(REF) 6.4-7.2 V;
- audio at the settled 8 ohm load at least 1 V pp.

The current run passes the IF period and detector plateau criteria. It fails the oscillator amplitude and current criteria. D6 current and settled reference-rail levels without `.ic` are not present in the supplied measurements. Audio is not assessed because N010 and C25 did not settle in the 12 ms window.

## Blocking items before routing

- Oscillator overdrive. V(Q6_C) is 0-4 V and Ie(Q6) reaches about +/-6 mA. Do not freeze the board before the BFT92 bias and feedback ratio are corrected and verified.
- Tank tracking. With one tuning voltage the L1-L2 frequency difference changes from about 0.5 to 1.5 MHz instead of remaining at 425 kHz. Independent correction or trimmers are required.
- Tuning travel. The present BB844 and 13.7 pF network gives about 0.8 MHz and cannot cover 88-108 MHz. Coarse tuning, switched L2, or another capacitance range is required.
- The revision 04 limiter blocker remains open: a 3 ms run with VBE(VT5) no lower than -5 V has not been completed.

Node names of the n0XX form are not normative. Before a run, assign the labels A, B, REF, TUNE, Q1_E, Q2_B, Q3_B, Q4_C, Q5_C, Q6_C, DETEC, AFC, FILT, N010, SPK, VZ_3V3, and VZ_6V8.

## Identifier correspondence table

The table is normative until KiCad is renumbered.

| Function | KiCad/README | LTspice rev 05 | Value or type |
|---|---|---|---|
| RF transistor | VT1 2N5401 | Q1 2N5401 | unchanged bias |
| Mixer | VT2 | Q2 2SC3838K | switching mixer |
| IF amplifier | VT3 / VT4 | Q3 / Q4 BC547C | group C |
| Limiter | VT5 | Q5 BC547C | group C |
| Oscillator | VT6 BFT92 | Q6 BFT92 | PNP, SOT-23 |
| Detector diodes | VD1 / VD2 | D2 / D3 1N4148 | unchanged |
| Tuning reference | VD3 / R19 | D6 BZX55C6V8 / R25 180 ohm | about 6.86 V |
| 3.3 V rail | VD4 / R27 | D4 / R19 1 kOhm | VZ_3V3 |
| Input varicap | BB844 / C4 | D1 BB844 / C4 13.7 pF | Cjo = 120 pF |
| Oscillator varicap | BB844 / C19 | D5 BB844 / C19 13.7 pF | Cjo = 120 pF |
| Input tank | L1 / C3 / C4 / D1 | 175 nH / 4.1 pF / 13.7 pF / BB844 | rev 05 |
| Oscillator tank | L2 / C17 / C18 / C19 / D5 | 138 nH / 10 pF / 36 pF / 13.7 pF / BB844 | rev 05 |
| Mixer load | 3 kOhm / 47 pF | R5 / C6 | 47 pF mandatory |
| IF attenuator | series resistor | R6 100 kOhm | unchanged |
| IF feedback | emitter-to-base | R7 2.2 kOhm | unchanged |
| Detector filter | R12 / C14 | 10 kOhm / 10 nF | rev 05 names |
| AFC | R22 / C22 | 15 kOhm / 47 uF | about 0.705 s |
| LM386 output capacitor | output coupling | C25 330 uF | settling exceeds short window |
| LM386 bypass | bypass node | C27 | not settled in the current run |

Sections 1-5 describe the LTspice revision 05 chain. Section 6 covers the LM386 stage in both the model and the product. Section 7 combines the LTspice rail topology with requirements that apply to the physical board.

## Architecture

```text
AE1 -> C6 -> Q1 / L1 / D1 -> Q2 -> Q3 -> Q4 -> Q5
                                                    |
                  LM386 <- volume <- detector <- D2 / D3 / C13
                    |                         |
                 C25 / 8R              R22 / C22 AFC
                                              |
                                 D1 / D5 / Q6 / L2
```

The antenna signal is amplified by a common-base RF stage and mixed with the oscillator through magnetic coupling between L1 and L2. The wideband untuned IF chain is followed by a limiter and a charge-pump frequency detector. The slow detector component drives the two BB844 tuning branches through AFC. The audio amplifier is an LM386.

Revision 05 parts are Q1 2N5401, Q2 2SC3838K, Q3-Q5 BC547C, Q6 BFT92, and D1/D5 BB844.

```math
f_{IF} \approx 425 \text{ kHz}, \qquad f_{LO} = f_{RF} + 425 \text{ kHz}
```

At 101.5 MHz RF the target oscillator is about 101.925 MHz. A 2.35 us period represents 425 kHz. The low IF places the image only about 850 kHz away, inside the front-end bandwidth. Better image rejection requires a two-tank preselector or dual conversion.

## Power rails

Node A feeds the limiter. Node B feeds Q1-Q4. The LM386 uses +9 V with local decoupling. The BFT92 oscillator uses VZ_3V3. The tuning reference uses the 6.8 V zener fed from +9 V through 180 ohm.

| Rail | Function | Normal level |
|---|---|---|
| +9 V | LM386 and references | 9.0 V |
| Node A | limiter | after input decoupling |
| Node B | Q1-Q4 | about 8.25-8.3 V |
| VZ_3V3 | BFT92 oscillator | 3.3 V |
| VZ_6V8 / REF | tuning and AFC | about 6.86 V |

The quiescent current of about 23 mA refers to the chain ahead of the LM386. Total product current and dissipation depend on volume setting and on the 8 ohm load.

## 1. Input RF amplifier

Q1 is a common-base 2N5401 stage. The antenna signal enters the emitter through 1 nF. A 6.8 kOhm / 33 kOhm divider sets base bias, 10 nF bypasses the base at RF, and 470 ohm sets the emitter current. The collector is loaded by the tank.

The revision 05 tank is L1 = 175 nH with C3 = 4.1 pF and the C4 = 13.7 pF plus D1 BB844 branch. The D1 reverse bias comes from the tuning network through a series resistor. These values are LTspice values and do not replace measurement of the real inductance, parasitic capacitance, and loaded Q.

```math
C(V) = \frac{C_{jo}}{(1 + V/V_j)^M}, \qquad C_{jo}=120 \text{ pF}, \quad V_j=0.75 \text{ V}, \quad M=1.35
```

The model curve was checked against the reference table to within 1 percent. Real tracking still depends on inductance, parasitic capacitance, and component spread.

In revision 05 Ie(Q1) is about -1.47 mA. V(Q1_E) carries a 101.5 MHz signal from 0 to about 400 mV, confirming delivery to the mixer input.

Coil L1 is wound with 0.5 mm wire on a 5.5 mm mandrel. Turn count and pitch must be chosen from a measured 175 nH rather than copied from the revision 04 calculation.

## 2. Mixer

Q2 is a 2SC3838K common-emitter switching mixer. A 620 kOhm resistor sets base current, 3 kOhm is the collector load, and 47 pF suppresses RF residue while setting the upper bound of the low IF. The IF leaves through a coupling network and a 100 kOhm attenuator.

```math
f_p = \frac{1}{2\pi \times 3\text{ kOhm} \times 47\text{ pF}} \approx 1.13 \text{ MHz}
```

The 47 pF capacitor is mandatory because it prevents LO residue from latching the IF amplifier. The debug signature of its absence is a Q3 collector below 0.3 V with the oscillator running.

Revision 05 V(Q2_B) is about 350-900 mV and Ic(Q2) about 0.3-3.6 mA. The mixer switches, but oscillator injection is excessive. Correct Q6 before changing the IF attenuation.

The input-tank coupling capacitor must be in the single-pF range. The historical 1 nF value and a 2.2 uF electrolytic on the RF node must not be fitted.

Magnetic L1-L2 coupling remains bidirectional. The board needs controlled coil orientation and spacing. SPICE does not derive the coupling coefficient from board geometry.

### Mixer post-filter

An additional low-pass section of 470 ohm and 33 pF belongs immediately after the mixer collector load:

```math
f_p = \frac{1}{2\pi \times 470 \times 33\text{ pF}} \approx 10.26 \text{ MHz}
```

It is nearly transparent at 425 kHz while reducing residual 88-108 MHz energy on the way into the IF amplifier. Its designators clashed with supply-decoupling parts in earlier versions and must be reassigned in KiCad.

## 3. IF amplifier

Q3 and Q4 remain the directly coupled BC547C pair. The 100 kOhm series attenuator and 2.2 kOhm emitter-to-base feedback resistor are retained. The Q4 emitter uses 470 ohm bypassed by 47 nF, and 10 nF couples to the limiter.

The 100 kOhm and 2.2 kOhm pair limits the drive and drains rectified charge within one IF cycle:

```math
\tau_{drain} \approx 2.2 \text{ kOhm} \times 1 \text{ nF} \approx 2.2 \text{ us}
```

That is shorter than the 2.35 us IF period, so charge does not accumulate on the coupling capacitor.

Revision 05 does not provide a separate Q3/Q4 DC table, so revision 04 amplitudes are not relabelled as current. Acceptance requires continuous IF pulses, no transition into a linear waveform, and no drift of the feedback-current mean.

## 4. Limiter and detector

Q5 is a BC547C limiter. A 47 kOhm resistor sets base current, 3 kOhm is the load, and the emitter returns to ground. Revision 05 V(Q5_C) is a 0-11 V pulse waveform with a 2.35 us period, corresponding to about 425 kHz.

Limiter reverse base-emitter voltage remains an open risk. A standard BJT model may not represent the real breakdown, so the item stays open until the 3 ms run with VBE(VT5) no lower than -5 V is complete.

The charge-pump detector uses C13 = 39 pF and two 1N4148 diodes:

```math
I_{avg} = C \times \Delta U \times f_{IF}, \qquad U_{det} = I_{avg} \times R_{load}
```

At about 425 kHz the expected plateau is near 1.2 V. V(DETEC) is 1.2 V and passes the 1.1-1.3 V criterion.

The revision 05 filter uses R12 = 10 kOhm and C14 = 10 nF:

```math
\tau_0 = 10 \text{ kOhm} \times 10 \text{ nF} = 100 \text{ us}
```

Under AFC loading the effective value is estimated near 60 us. A 4.7 nF alternative gives 47 us unloaded, but it is not adopted before the audio response and ripple level are measured.

## 5. Local oscillator and AFC

Q6 BFT92, L2 = 138 nH, C17 = 10 pF, C18 = 36 pF, D5 BB844, and C19 = 13.7 pF form the revision 05 Colpitts oscillator. The base is AC-grounded and the stage is fed from the regulated 3.3 V rail.

```math
C_s = \frac{10 \times 36}{10 + 36} \approx 7.83 \text{ pF}
```

The 2N5401 did not start at 101.9 MHz. The BFT92 starts, but V(Q6_C) is 0-4 V and Ie(Q6) reaches about +/-6 mA. The required values are 1-2 V pp and 2-3 mA without spikes. No correction value is normative yet because the supplied notes conflict on the direction and designator of the proposed C17/R16 changes.

The AFC network is R22 = 15 kOhm and C22 = 47 uF:

```math
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
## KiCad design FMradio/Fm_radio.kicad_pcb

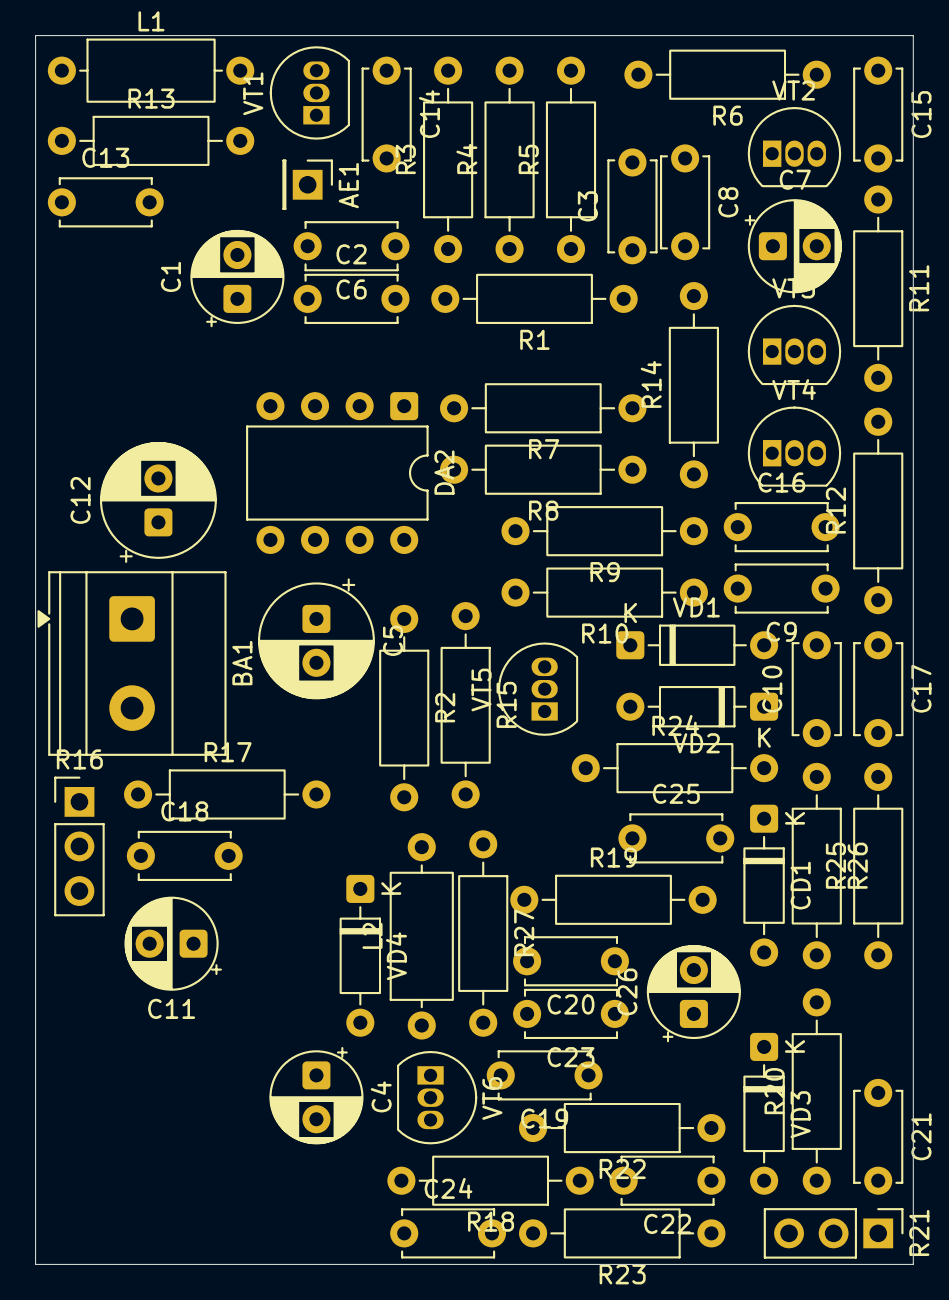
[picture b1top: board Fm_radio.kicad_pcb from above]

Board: 2 copper layers, 50.0 x 70.0 mm, 69 parts (0 on the bottom side), 32 nets, no tracks yet.

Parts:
AE1: Antenna; PinHeader_1x01_P2.54mm_Vertical
BA1: 8R; TerminalBlock_Phoenix_MKDS-1,5-2-5.08_1x02_P5.08mm_Horizont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
C1, C7: 10u; CP_Radial_D5.0mm_P2.50mm
C2, C21, C24, C25: 100n; C_Disc_D5.0mm_W2.5mm_P5.00mm
C3: 47; C_Disc_D5.0mm_W2.5mm_P5.00mm
C4, C11: 22u; CP_Radial_D5.0mm_P2.50mm
C5, C12: 220u; CP_Radial_D6.3mm_P2.50mm
C6, C15, C20: 1n; C_Disc_D5.0mm_W2.5mm_P5.00mm
C8, C9: 3.3n; C_Disc_D5.0mm_W2.5mm_P5.00mm
C10: 39; C_Disc_D5.0mm_W2.5mm_P5.00mm
C13, C17, C22: 10n; C_Disc_D5.0mm_W2.5mm_P5.00mm
C14: 8/30pF; C_Disc_D5.0mm_W2.5mm_P5.00mm
C16: 47n; C_Disc_D5.0mm_W2.5mm_P5.00mm
C18: 0.1; C_Disc_D5.0mm_W2.5mm_P5.00mm
C19: 8.2p; C_Disc_D5.0mm_W2.5mm_P5.00mm
C23: 36; C_Disc_D5.0mm_W2.5mm_P5.00mm
C26: 4.7u; CP_Radial_D5.0mm_P2.50mm
CD1: BB910; D_DO-35_SOD27_P7.62mm_Horizontal
DA2: LM386; DIP-8_W7.62mm
L1: 6T; L_Axial_L7.0mm_D3.3mm_P10.16mm_Horizontal_Fastron_MICC
L2: 5T; L_Axial_L7.0mm_D3.3mm_P10.16mm_Horizontal_Fastron_MICC
R1, R27: 1k; R_Axial_DIN0207_L6.3mm_D2.5mm_P10.16mm_Horizontal
R2: 22; R_Axial_DIN0207_L6.3mm_D2.5mm_P10.16mm_Horizontal
R3, R14, R19: 470; R_Axial_DIN0207_L6.3mm_D2.5mm_P10.16mm_Horizontal
R4: 6.8k; R_Axial_DIN0207_L6.3mm_D2.5mm_P10.16mm_Horizontal
R5, R10: 3k; R_Axial_DIN0207_L6.3mm_D2.5mm_P10.16mm_Horizontal
R6: 620; R_Axial_DIN0207_L6.3mm_D2.5mm_P10.16mm_Horizontal
R7, R15, R22: 10k; R_Axial_DIN0207_L6.3mm_D2.5mm_P10.16mm_Horizontal
R8: 2.2k; R_Axial_DIN0207_L6.3mm_D2.5mm_P10.16mm_Horizontal
R9: 47k; R_Axial_DIN0207_L6.3mm_D2.5mm_P10.16mm_Horizontal
R11: 33; R_Axial_DIN0207_L6.3mm_D2.5mm_P10.16mm_Horizontal
R12: 100k; R_Axial_DIN0207_L6.3mm_D2.5mm_P10.16mm_Horizontal
R13: 33k; R_Axial_DIN0207_L6.3mm_D2.5mm_P10.16mm_Horizontal
R16, R21: 10k; PinHeader_1x03_P2.54mm_Vertical
R17: 10; R_Axial_DIN0207_L6.3mm_D2.5mm_P10.16mm_Horizontal
R18: 20k; R_Axial_DIN0207_L6.3mm_D2.5mm_P10.16mm_Horizontal
R20, R24: 30k; R_Axial_DIN0207_L6.3mm_D2.5mm_P10.16mm_Horizontal
R23: 680; R_Axial_DIN0207_L6.3mm_D2.5mm_P10.16mm_Horizontal
R25, R26: 15k; R_Axial_DIN0207_L6.3mm_D2.5mm_P10.16mm_Horizontal
VD1, VD2: 1N4148; D_DO-35_SOD27_P7.62mm_Horizontal
VD3: KB168_NM; D_DO-35_SOD27_P7.62mm_Horizontal
VD4: BZX55C3V3; D_DO-35_SOD27_P7.62mm_Horizontal
VT1, VT6: 2N3906; TO-92_Inline
VT2: S9018; TO-92_Inline
VT3, VT4, VT5: BC547; TO-92_Inline

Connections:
+9V: C5.1, DA2.6, R2.1, R19.1, R27.1
GND: BA1.1, C1.2, C2.1, C4.2, C5.2, C13.1, C14.1, C16.1, C17.1, C21.2, C24.1, C25.1, C26.2, DA2.2, DA2.4, L1.1, L2.2, R13.1, R14.1, R15.1, R16.1, R17.1, R18.2, R21.1, R24.1, VD1.1, VD3.1, VD4.1, VT2.3, VT3.3, VT5.3
unnamed: AE1.1 (A_1), C6.2
unnamed: BA1.2, C12.2
unnamed: C1.1, C2.2, C3.2, R1.2, R3.2, R4.2, R5.2, R6.2
unnamed: C3.1, C8.1, R5.1, VT2.2
unnamed: C4.1, R1.1, R2.2, R7.2, R8.2, R9.2, R10.2
unnamed: C8.2, R11.1
unnamed: C9.1, R8.1, VT4.2
unnamed: C9.2, R9.1, VT5.1
unnamed: C10.1, VD1.2, VD2.1
unnamed: C10.2, R10.1, VT5.2
unnamed: C11.1, C17.2, R15.2, R26.1, VD2.2
unnamed: C11.2, R16.2
unnamed: C12.1, C18.1, DA2.5
unnamed: C6.1, C13.2, R3.1, R4.1, R13.2, VT1.1, VT1.3
unnamed: C7.2, C14.2, C15.2, L1.2, VT1.2
unnamed: C7.1, C15.1, R6.1, VT2.1
unnamed: C16.2, R12.1, R14.2, VT4.3
unnamed: C18.2, R17.2
unnamed: C19.1, C23.2, R23.2, VT6.3
unnamed: C19.2, C20.2, L2.1, VT6.2
unnamed: C20.1, CD1.2, R20.2
unnamed: C21.1, R20.1, R21.3
unnamed: C22.1, C23.1, C24.2, R22.1, R23.1, R27.2, VD4.2
unnamed: C22.2, R18.1, R22.2, VT6.1
unnamed: C25.2, CD1.1, R24.2, R25.2
unnamed: C26.1, R25.1, R26.2
unnamed: DA2.3, R16.3
unnamed: R7.1, VT3.2, VT4.1
unnamed: R11.2, R12.2, VT3.1
unnamed: R19.2, R21.2, VD3.2
